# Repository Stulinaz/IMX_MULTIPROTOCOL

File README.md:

# IMX_MULTIPROTOCOL
imxrt1020 usb to i2c, uart, spi. project for nxp hackathon contest. based on nimxrt1020-evk.

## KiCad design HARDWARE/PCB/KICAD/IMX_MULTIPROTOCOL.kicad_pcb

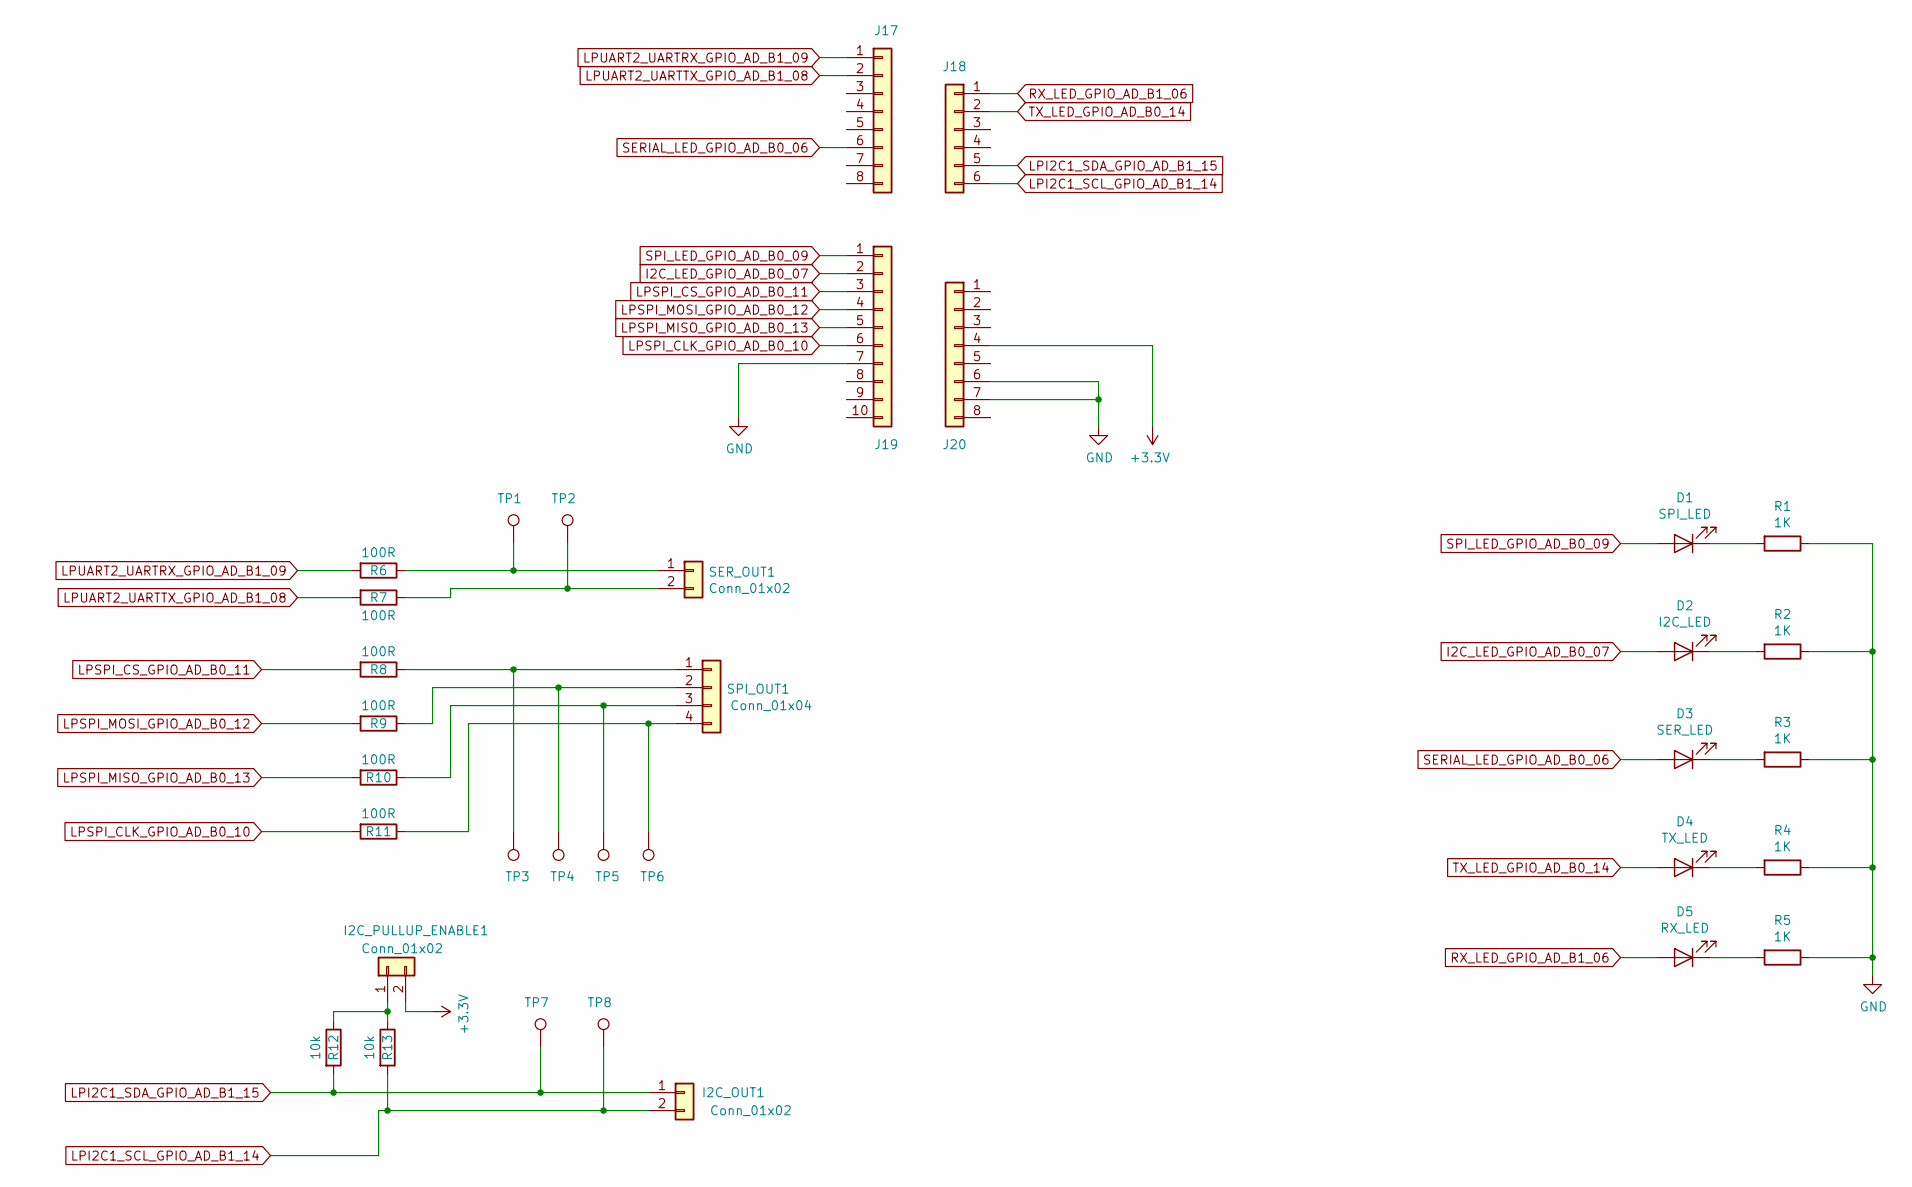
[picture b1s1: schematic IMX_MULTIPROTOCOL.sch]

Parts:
D1: SPI_LED; R_0805_2012Metric_Pad1.15x1.40mm_HandSolder
D2: I2C_LED; R_0805_2012Metric_Pad1.15x1.40mm_HandSolder
D3: SER_LED; R_0805_2012Metric_Pad1.15x1.40mm_HandSolder
D4: TX_LED; R_0805_2012Metric_Pad1.15x1.40mm_HandSolder
D5: RX_LED; R_0805_2012Metric_Pad1.15x1.40mm_HandSolder
I2C_OUT1, I2C_PULLUP_ENABLE1: Conn_01x02; PinHeader_1x02_P2.54mm_Vertical
J17, J20: Conn_01x08; PinHeader_1x08_P2.54mm_Vertical
J18: Conn_01x06; PinHeader_1x06_P2.54mm_Vertical
J19: Conn_01x10; PinHeader_1x10_P2.54mm_Vertical
R1, R2, R3, R4, R5: 1K; R_0805_2012Metric_Pad1.15x1.40mm_HandSolder
R6, R7, R8, R9, R10, R11: 100R; R_0805_2012Metric_Pad1.15x1.40mm_HandSolder
R12, R13: 10k; R_0805_2012Metric_Pad1.15x1.40mm_HandSolder
SER_OUT1: Conn_01x02; PinHeader_1x02_P2.54mm_Vertical
SPI_OUT1: Conn_01x04; PinHeader_1x04_P2.54mm_Vertical
TP1, TP2, TP3, TP4, TP5, TP6, TP7, TP8: TestPoint; TestPoint_Pad_D1.5mm

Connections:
+3V3: I2C_PULLUP_ENABLE1.2, J20.4
GND: J19.7, J20.6, J20.7, R1.1, R2.1, R3.1, R4.1, R5.1
I2C_LED_GPIO_AD_B0_07: D2.2 (A), J19.2
LPI2C1_SCL_GPIO_AD_B1_14: I2C_OUT1.2, J18.6, R13.2, TP8.1
LPI2C1_SDA_GPIO_AD_B1_15: I2C_OUT1.1, J18.5, R12.2, TP7.1
LPSPI_CLK_GPIO_AD_B0_10: J19.6, R11.2
LPSPI_CS_GPIO_AD_B0_11: J19.3, R8.2
LPSPI_MISO_GPIO_AD_B0_13: J19.5, R10.2
LPSPI_MOSI_GPIO_AD_B0_12: J19.4, R9.2
LPUART2_UARTRX_GPIO_AD_B1_09: J17.1, R6.2
LPUART2_UARTTX_GPIO_AD_B1_08: J17.2, R7.2
unnamed: D1.1 (K), R1.2
unnamed: D2.1 (K), R2.2
unnamed: D3.1 (K), R3.2
unnamed: D4.1 (K), R4.2
unnamed: D5.1 (K), R5.2
unnamed: I2C_PULLUP_ENABLE1.1, R12.1, R13.1
unnamed: R6.1, SER_OUT1.1, TP1.1
unnamed: R7.1, SER_OUT1.2, TP2.1
unnamed: R8.1, SPI_OUT1.1, TP3.1
unnamed: R9.1, SPI_OUT1.2, TP4.1
unnamed: R10.1, SPI_OUT1.3, TP5.1
unnamed: R11.1, SPI_OUT1.4, TP6.1
RX_LED_GPIO_AD_B1_06: D5.2 (A), J18.1
SERIAL_LED_GPIO_AD_B0_06: D3.2 (A), J17.6
SPI_LED_GPIO_AD_B0_09: D1.2 (A), J19.1
TX_LED_GPIO_AD_B0_14: D4.2 (A), J18.2

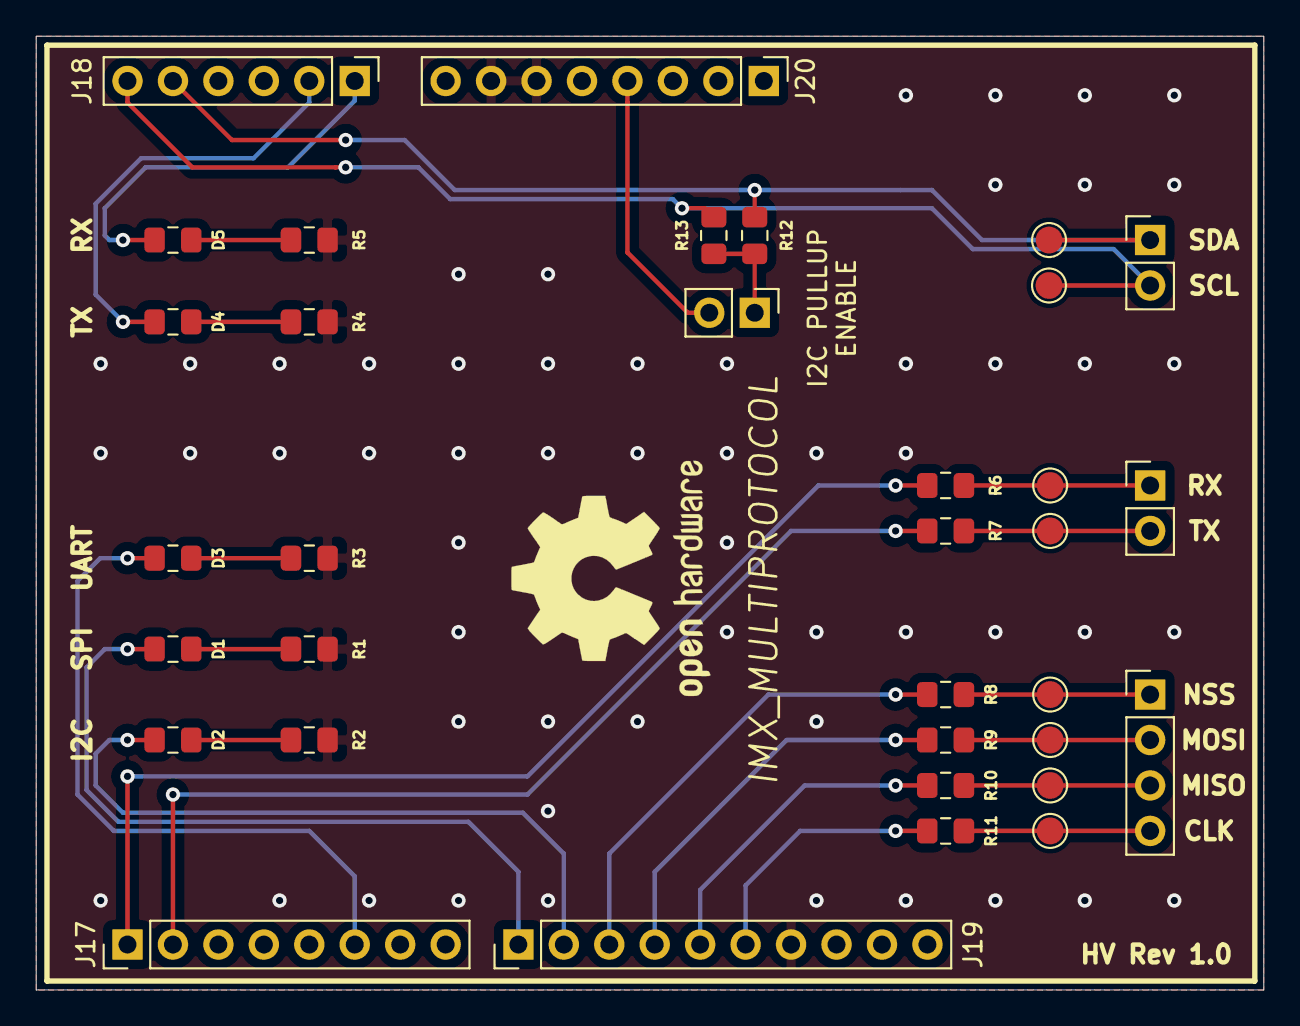
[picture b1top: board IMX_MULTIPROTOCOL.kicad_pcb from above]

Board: 2 copper layers, 68.6 x 53.3 mm, 34 parts (0 on the bottom side), 27 nets.

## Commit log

2021-05-04 PROJECT BUILD
2021-05-06 FIRMWARE: add gpt, led_manager, buffers_manager
    HARDWARE: No change
2021-05-06 FIRMWARE: add lpuart, command_ process. improved USB.
    HARDWARE:
    no change
    DOC:
    no change
2021-05-11 FIRMWARE: USB fix, Led rework,
    HARDWARE: Led rework
2021-05-12 FIRMWARE: Added SPI
    HARDWARE: No change
    DOC: No change
2021-05-18 FIRMWARE: USB sync on rx serial, SPI nss driven manually
    HARDWARE: No change
    DOC: ADDED Welcome
2021-05-22 IMX_MULTIPROTOCOL_v001
    FIRMWARE: I2C Fix
    HARDWARE: No change
    DOC: In progress
2021-06-18 IMX_MULTIPROTOCOL_v002
    First Release
2021-11-05 added_readme_photo
